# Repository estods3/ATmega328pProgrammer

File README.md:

# ATmega328pProgrammer
A Schematic and PCB Design for an Arduino Nano based ATmega328p/Arduino Programmer

## Steps

1) Program your Arduino Nano using the SW/ArduinoISP/ArduinoISP.ino script in the Arduino IDE. NOTE: Do this BEFORE placing you Arduino Nano in the circuit made from this repository. The circuit in the repo disables the auto-reset function of the Nano using a capacitor from reset to ground. This will allow the Nano to act as a programmer using the SW/ArduinoISP/ArduinoISP.ino script.
2) Build the circuit outlined in the PCB folder. The schematic and board layout can be opened using Eagle.
3) Insert an Arduino Nano into the header pins of the board with USB port facing opposite of the 3 LEDs on the board. Make sure the Nano is powered off and not plugged into a PC or other USB device. Next, add an ATmega328p chip into the header pins with the notch facing to the left.
4) Plug in the USB cable from the Nano to the PC. Open the Arduino IDE and select "Arduino Uno" as the board under Tools. Select the port as the correct port for your Nano. These settings will be used to burn the bootloader for an Arduino Uno to the ATmega chip.
5) Burn the Bootloader. This will take a few seconds. Check red LED for errors.
6) Upload the test script (SW/Blink/Blink.ino) to test that the bootloader was burned successfully and the chip can now accept programs. Open the test script included in this repo in the Arduino IDE. Use the same settings as in step 4. Click "Sketch" then "Upload using Programmer" to upload the test script to the chip. The Test LED should begin to blink.

## Resources
https://docs.arduino.cc/built-in-examples/arduino-isp/ArduinoToBreadboard

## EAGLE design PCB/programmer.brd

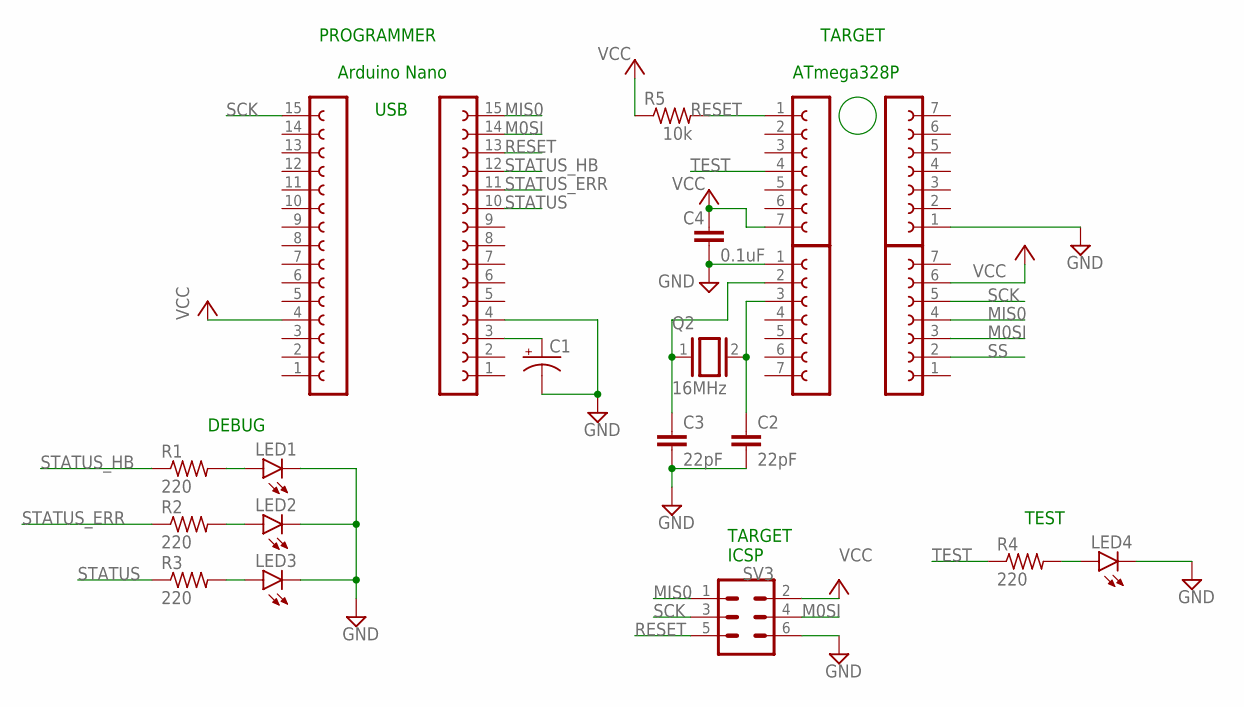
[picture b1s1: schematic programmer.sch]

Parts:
C1: CPOL-US153CLV-0405; 153CLV-0405
C2, C3: 22pF; C2.5-3
C4: 0.1uF; C2.5-3
LED1, LED2, LED3, LED4: LED5MM
Q2: 16MHz; QS
R1, R2, R3, R4: 220; 0207/7
R5: 10k; 0207/7
SV1, SV2: FE15-1; FE15
SV3: MA03-2
SV6, SV7, SV8, SV9: FE07-1; FE07

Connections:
GND: C1.-, C2.2, C3.2, C4.2, LED1.K (C), LED2.K (C), LED3.K (C), LED4.K (C), SV1.4, SV3.6, SV7.1, SV8.1
M0SI: SV1.14, SV3.4, SV9.3
MIS0: SV1.15, SV3.1, SV9.4
unnamed: C1.+, SV1.3
unnamed: LED1.A, R1.2
unnamed: LED4.A, R4.2
unnamed: LED3.A, R3.2
unnamed: LED2.A, R2.2
unnamed: C2.1, Q2.2, SV7.3
unnamed: C3.1, Q2.1, SV7.2
RESET: R5.2, SV1.13, SV3.5, SV6.1
SCK: SV2.15, SV3.3, SV9.5
SS: SV9.2
STATUS: R3.1, SV1.10
STATUS_ERR: R2.1, SV1.11
STATUS_HB: R1.1, SV1.12
TEST: R4.1, SV6.4
VCC: C4.1, R5.1, SV2.4, SV3.2, SV6.7, SV9.6

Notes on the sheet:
Arduino Nano
PROGRAMMER
ATmega328P
TARGET
TARGET ICSP
DEBUG
TEST
USB

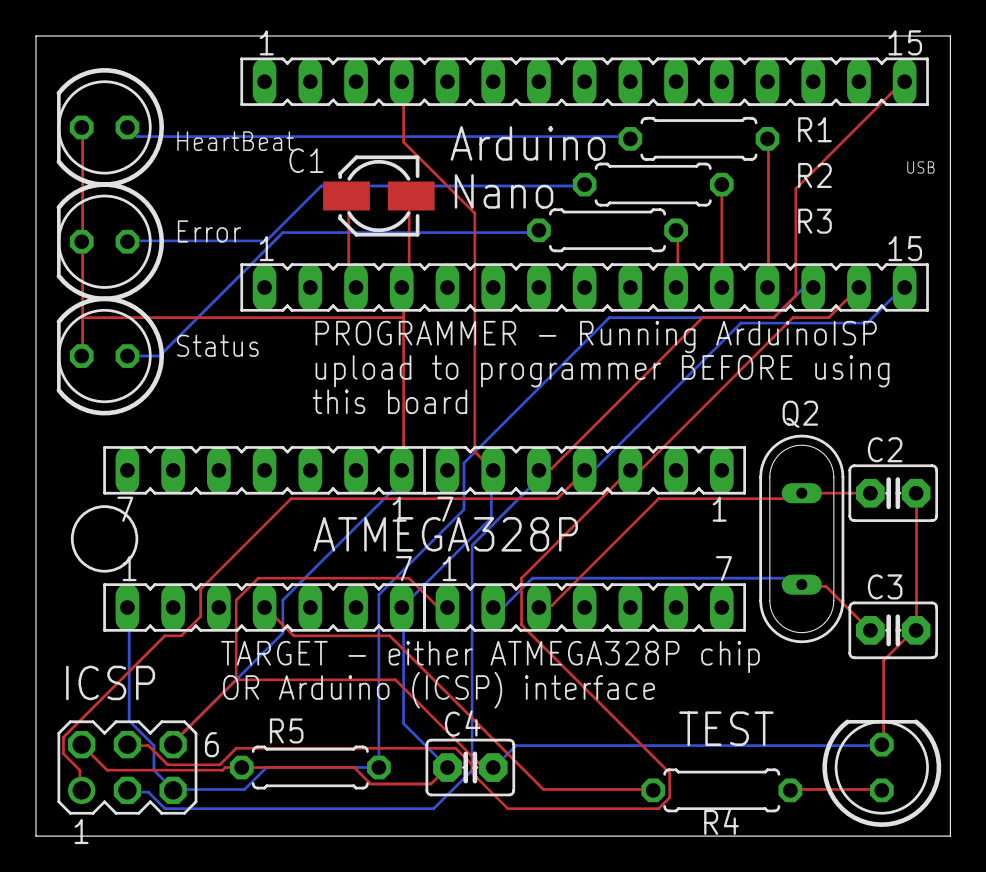
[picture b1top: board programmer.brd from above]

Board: 2 copper layers, 50.8 x 44.5 mm, 21 parts (0 on the bottom side), 17 nets.

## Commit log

2022-02-22 added test program Blink.ino
2022-02-22 added built programmer jpg
